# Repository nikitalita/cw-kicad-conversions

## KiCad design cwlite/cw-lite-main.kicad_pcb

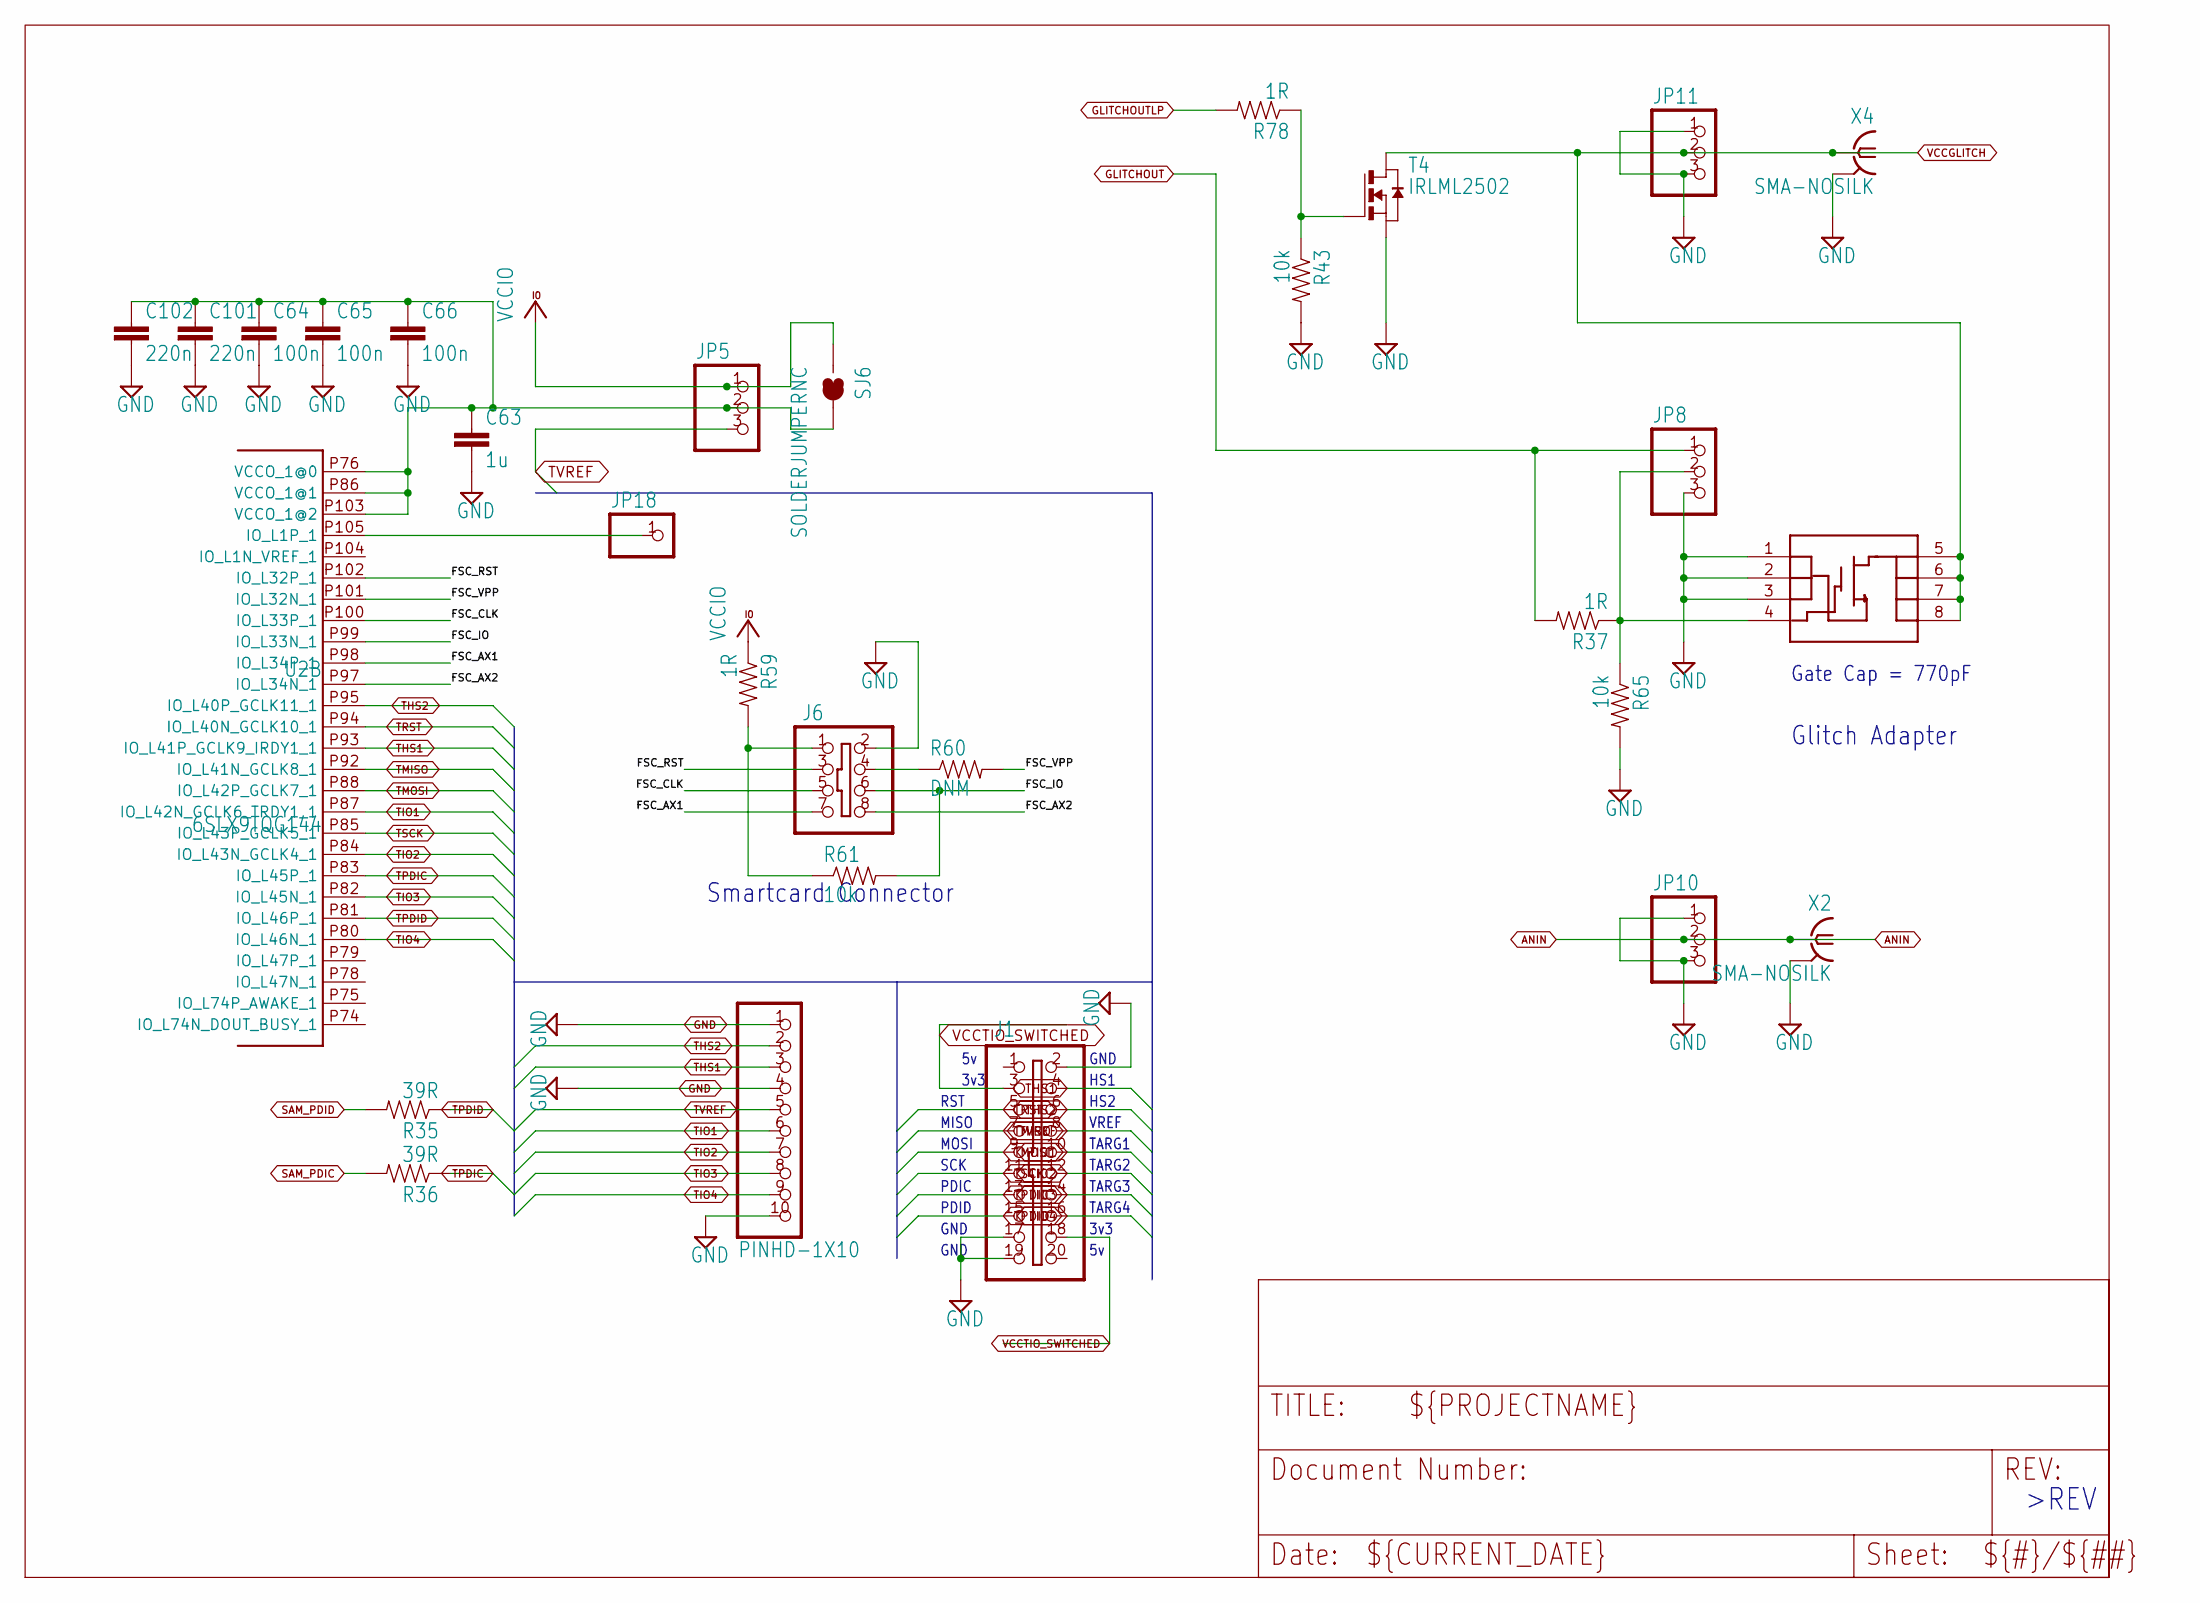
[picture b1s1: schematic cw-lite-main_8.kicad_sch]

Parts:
C63: 1u; 0603C
C64, C65, C66: 100n; 0402C
C101, C102: 220n; 0402C
J1: SHROUD_2X10-SHROUDED; PINSHRD_PTH_2X10
J6: SHROUD_2X4SHROUD; PINSHRD_PTH_2X04
JP5, JP8, JP10, JP11: PINHD-1X3; 1X03
JP9: PINHD-1X10; 1X10-BIG
JP18: PINHD-1X1; 1X01
R35, R36: 39R; 0603R
R37, R59, R78: 1R; 0603R
R43, R61, R65: 10k; 0603R
R60: DNM; 0603R
SJ6: SOLDERJUMPERNC; SJ_2S
T4: IRLML2502; SOT-23; MPN IRLML2502TRPBF
U2: 6SLX9TQG144; TQ144; MPN XC6SLX9-3TQG144C
U8: MOSFET-NCHANNEL-SOIC8; SO08
X2, X4: SMA-NOSILK; J502-ND-142-0711-821_826-NOSILK

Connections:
/cw-lite-main_8/FSC_AX1: J6.7, U2.P98 (IO_L34P_1)
/cw-lite-main_8/FSC_AX2: J6.8, U2.P97 (IO_L34N_1)
/cw-lite-main_8/FSC_CLK: J6.5, U2.P100 (IO_L33P_1)
/cw-lite-main_8/FSC_IO: J6.6, R61.2, U2.P99 (IO_L33N_1)
/cw-lite-main_8/FSC_RST: J6.3, U2.P102 (IO_L32P_1)
/cw-lite-main_8/FSC_VPP: R60.2, U2.P101 (IO_L32N_1)
ANIN: JP10.2, X2.1; also elsewhere on the board
GLITCHOUT: JP8.1, R37.2; also elsewhere on the board
GLITCHOUTLP: R78.2; also elsewhere on the board
GND: C63.2, C64.2, C65.2, C66.2, C101.2, C102.2, J1.2, J1.17, J1.19, J6.2, JP8.3, JP9.1, JP9.4, JP9.10, JP10.1, JP10.3, JP11.1, JP11.3, R43.2, R65.2, T4.2 (S), U8.1 (S@1), U8.2 (S@2), U8.3 (S@3), X2.G@1 (2), X2.G@2 (2), X2.G@3 (2), X2.G@4 (2), X4.G@1 (2), X4.G@2 (2), X4.G@3 (2), X4.G@4 (2); also elsewhere on the board
unnamed: J6.1, R59.2, R61.1
unnamed: J6.4, R60.1
unnamed: R43.1, R78.1, T4.3 (G)
unnamed: JP18.1, U2.P105 (IO_L1P_1)
unnamed: C63.1, C64.1, C65.1, C66.1, C101.1, C102.1, JP5.2, SJ6.2, U2.P76 (VCCO_1@0), U2.P86 (VCCO_1@1), U2.P103 (VCCO_1@2)
unnamed: JP8.2, R37.1, R65.1, U8.4 (G)
SAM_PDIC: R36.2; also elsewhere on the board
SAM_PDID: R35.2; also elsewhere on the board
THS1: J1.4, JP9.3, U2.P93 (IO_L41P_GCLK9_IRDY1_1); also elsewhere on the board
THS2: J1.6, JP9.2, U2.P95 (IO_L40P_GCLK11_1); also elsewhere on the board
TIO1: J1.10, JP9.6, U2.P87 (IO_L42N_GCLK6_TRDY1_1); also elsewhere on the board
TIO2: J1.12, JP9.7, U2.P84 (IO_L43N_GCLK4_1); also elsewhere on the board
TIO3: J1.14, JP9.8, U2.P82 (IO_L45N_1); also elsewhere on the board
TIO4: J1.16, JP9.9, U2.P80 (IO_L46N_1); also elsewhere on the board
TMISO: J1.7, U2.P92 (IO_L41N_GCLK8_1); also elsewhere on the board
TMOSI: J1.9, U2.P88 (IO_L42P_GCLK7_1); also elsewhere on the board
TPDIC: J1.13, R36.1, U2.P83 (IO_L45P_1); also elsewhere on the board
TPDID: J1.15, R35.1, U2.P81 (IO_L46P_1); also elsewhere on the board
TRST: J1.5, U2.P94 (IO_L40N_GCLK10_1); also elsewhere on the board
TSCK: J1.11, U2.P85 (IO_L43P_GCLK5_1); also elsewhere on the board
TVREF: J1.8, JP5.3, JP9.5; also elsewhere on the board
VCCGLITCH: JP11.2, T4.1 (D), U8.5 (D@4), U8.6 (D@3), U8.7 (D@2), U8.8 (D@1), X4.1; also elsewhere on the board
VCCIO: JP5.1, R59.1, SJ6.1; also elsewhere on the board
VCCTIO_SWITCHED: J1.3, J1.18; also elsewhere on the board

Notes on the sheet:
3v3
Glitch Adapter
VREF
PDID
RST
>REV
SCK
HS1
Smartcard Connector
TARG1
MOSI
Gate Cap = 770pF
GND
TARG2
TARG3
MISO
HS2
PDIC
TARG4

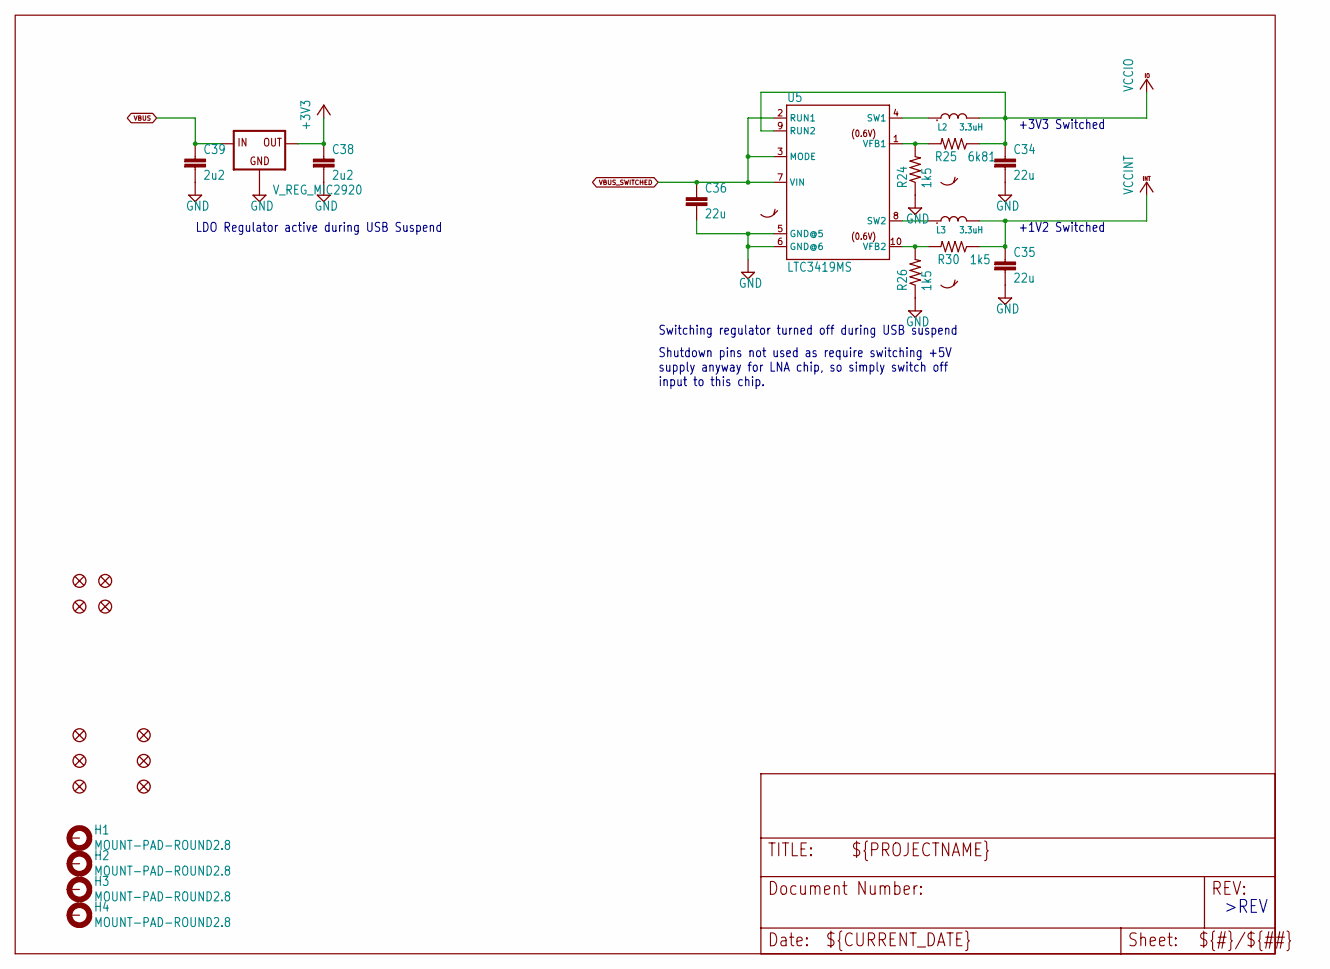
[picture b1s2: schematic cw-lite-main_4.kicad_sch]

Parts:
C34, C35, C36: 22u; 0805
C38, C39: 2u2; 0603C
FID1, FID2, FID3, FID4, FID5, FID6: FIDUCIAL1.5X3; FIDUCIAL-1.5X3
H1, H2, H3, H4: MOUNT-PAD-ROUND2.8; 2,8-PAD
L2: 3.3uH; VLS3015
L3: 3.3uH; VLS3015; MPN VLS3015ET-3R3M
MFID1, MFID2, MFID3, MFID4: FIDUCIALUFIDUCIAL; MICRO-FIDUCIAL
R24, R26, R30: 1k5; 0402R
R25: 6k81; 0402R
U5: LTC3419MS; MSOP10; MPN LTC3419EMS#PBF
U7: V_REG_MIC2920; SOT223; MPN TC1262-3.3VDBTR

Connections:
+3V3: C38.1, U7.3 (OUT); also elsewhere on the board
GND: C34.2, C35.2, C36.2, C38.2, C39.2, R24.1, R26.1, U5.5 (GND@5), U5.6 (GND@6), U7.2 (GND); also elsewhere on the board
unnamed: L2.1, U5.4 (SW1)
unnamed: L3.1, U5.8 (SW2)
unnamed: R24.2, R25.2, U5.1 (VFB1)
unnamed: R26.2, R30.2, U5.10 (VFB2)
VBUS: C39.1, U7.1 (IN); also elsewhere on the board
VBUS_SWITCHED: C36.1, U5.2 (RUN1), U5.3 (MODE), U5.7 (VIN); also elsewhere on the board
VCCINT: C35.1, L3.2, R30.1; also elsewhere on the board
VCCIO: C34.1, L2.2, R25.1, U5.9 (RUN2); also elsewhere on the board

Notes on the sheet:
Switching regulator turned off during USB suspend
LDO Regulator active during USB Suspend
+3V3 Switched
>REV
+1V2 Switched
Shutdown pins not used as require switching +5V supply anyway for LNA chip, so simply switch off input to this chip.

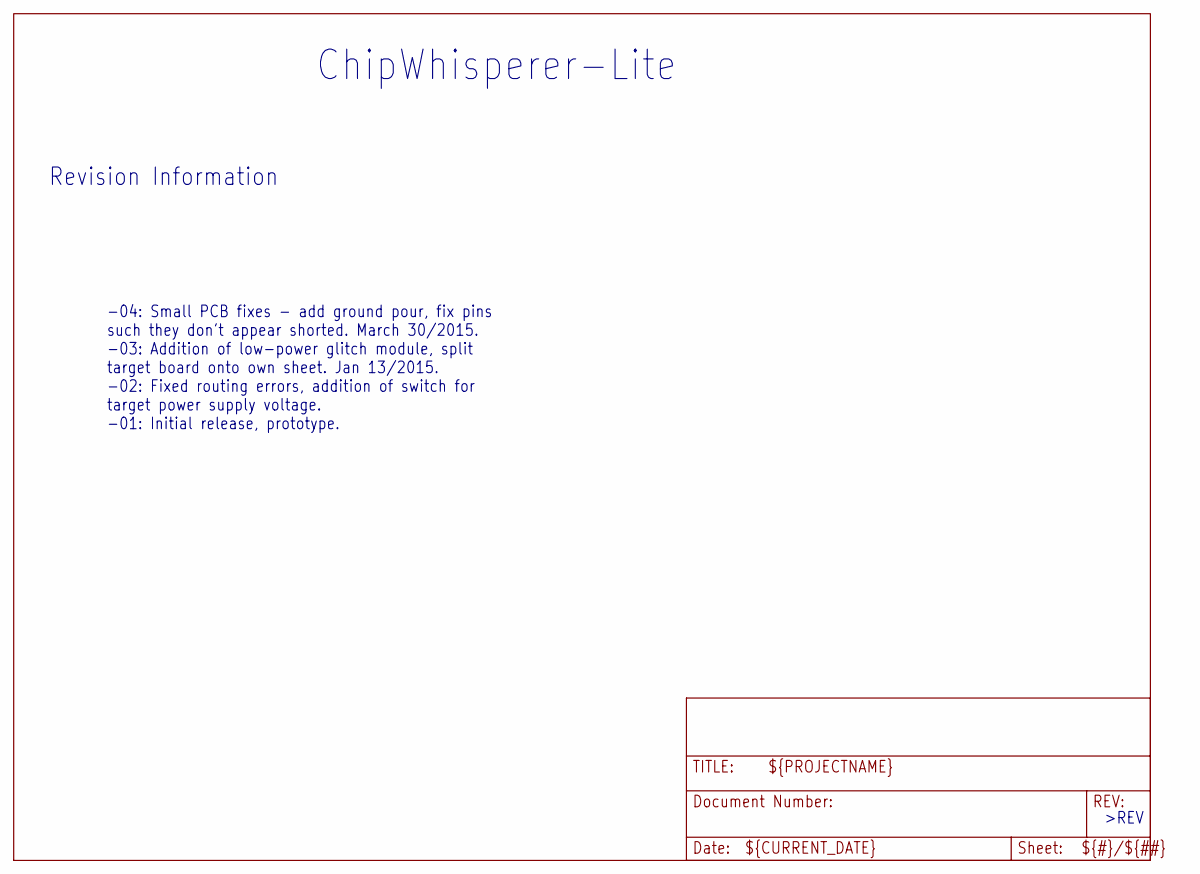
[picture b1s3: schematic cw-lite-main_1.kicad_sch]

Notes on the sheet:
ChipWhisperer-Lite
-04: Small PCB fixes - add ground pour, fix pins such they don't appear shorted. March 30/2015. -03: Addition of low-power glitch module, split target board onto own sheet. Jan 13/2015. -02: Fixed routing errors, addition of switch for target power supply voltage. -01: Initial release, prototype.
>REV
Revision Information

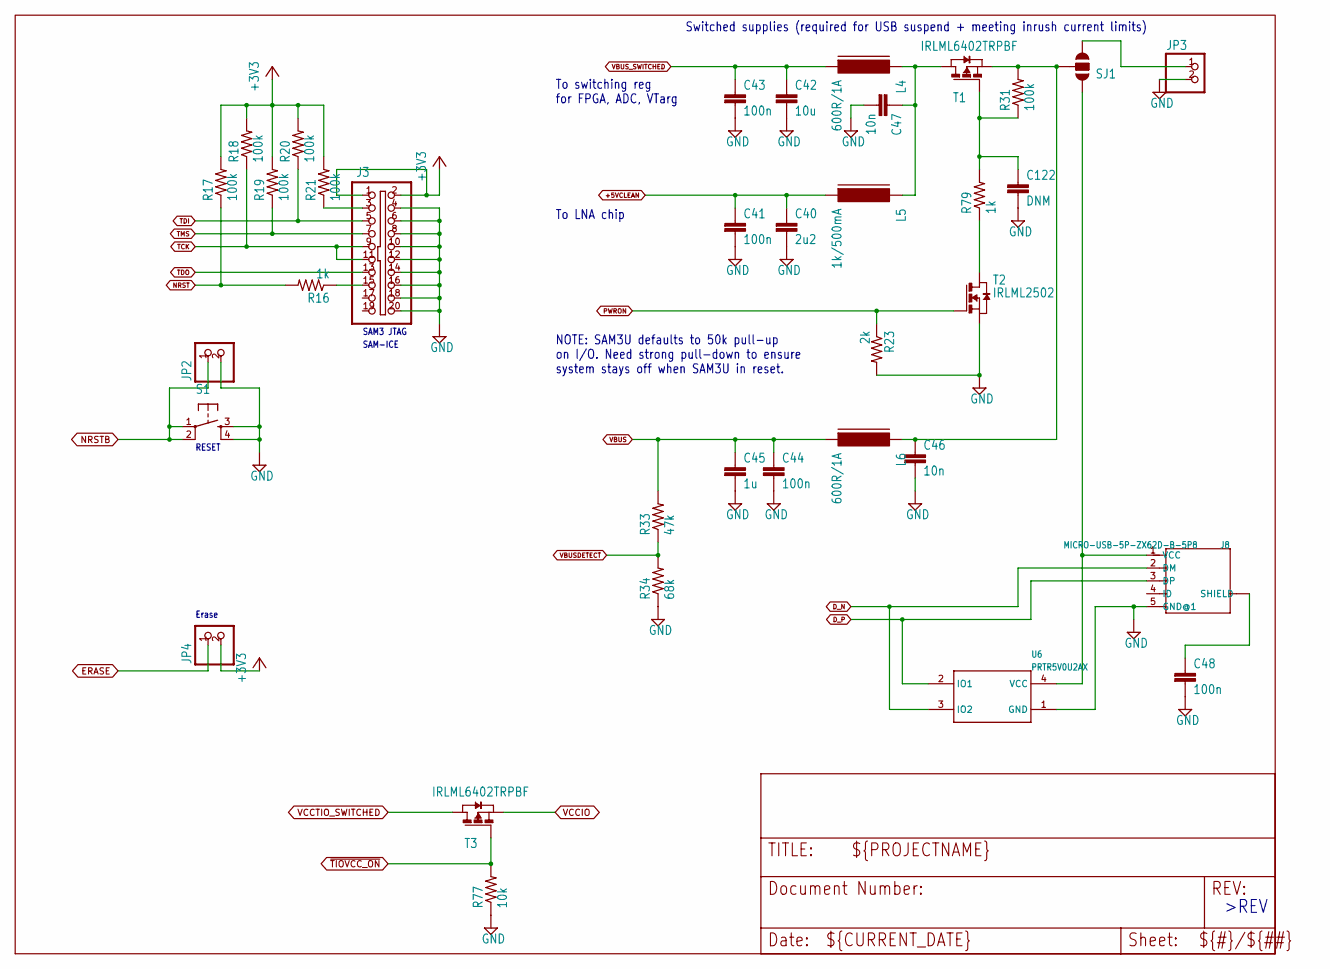
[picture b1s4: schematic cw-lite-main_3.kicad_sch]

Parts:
C40: 2u2; 0603C
C41, C43, C44, C48: 100n; 0603C
C42: 10u; 0603C
C45: 1u; 0603C
C46, C47: 10n; 0603C
C122: DNM; 0603C
J3: SHROUD_2X10-SHROUDED; PINSHRD_PTH_2X10
J8: MICRO-USB-5P-ZX62D-B-5P8; B-SMD-5P-TH; MPN ZX62D-B-5P8
JP2, JP3, JP4: PINHD-1X2; 1X02
L4, L6: 600R/1A; FB603
L5: 1k/500mA; FB603
R16: 1k; 0402R
R17, R18, R19, R20, R21, R31: 100k; 0402R
R23: 2k; 0603R
R33: 47k; 0402R
R34: 68k; 0402R
R77: 10k; 0402R
R79: 1k; 0603R
S1: TAC_SWITCHSMD; TACTILE_SWITCH_SMD
SJ1: SOLDERJUMPER_2WAYPASTE1&2; SJ_3_PASTE1&2
T1, T3: IRLML6402TRPBF; SOT-23; MPN IRLML6402TRPBF
T2: IRLML2502; SOT-23; MPN IRLML2502TRPBF
U6: PRTR5V0U2AX; SOT143B; MPN PRTR5V0U2AX,215

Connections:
+3V3: J3.1, J3.2, JP4.2, R17.2, R18.2, R19.2, R20.2, R21.2; also elsewhere on the board
+5VCLEAN: C40.1, C41.1, L5.2; also elsewhere on the board
D_N: J8.2 (DM), U6.3 (IO2); also elsewhere on the board
D_P: J8.3 (DP), U6.2 (IO1); also elsewhere on the board
ERASE: JP4.1; also elsewhere on the board
GND: C40.2, C41.2, C42.2, C43.2, C44.2, C45.2, C46.2, C47.2, C48.2, C122.2, J3.4, J3.6, J3.8, J3.10, J3.12, J3.14, J3.16, J3.18, J3.20, J8.5 (GND@1), JP2.2, JP3.2, R23.2, R34.1, R77.1, S1.3, S1.4, T2.2 (S), U6.1 (GND); also elsewhere on the board
NRST: R16.2, R17.1; also elsewhere on the board
NRSTB: JP2.1, S1.1, S1.2; also elsewhere on the board
unnamed: C48.1, J8.E1 (SHIELD), J8.E2 (SHIELD), J8.P$1 (SHIELD), J8.P$2 (SHIELD), J8.P$3 (SHIELD), J8.P$4 (SHIELD)
unnamed: J3.3, R21.1
unnamed: J3.15, R16.1
unnamed: J8.1 (VCC), SJ1.1, U6.4 (VCC)
unnamed: JP3.1, SJ1.3
unnamed: C47.1, L4.1, L5.1, T1.1 (D)
unnamed: C122.1, R31.1, R79.2, T1.3 (G)
unnamed: C46.1, L6.1, R31.2, SJ1.2, T1.2 (S)
unnamed: R79.1, T2.1 (D)
PWRON: R23.1, T2.3 (G); also elsewhere on the board
TCK: J3.9, J3.11, R18.1; also elsewhere on the board
TDI: J3.5, R20.1; also elsewhere on the board
TDO: J3.13; also elsewhere on the board
TMS: J3.7, R19.1; also elsewhere on the board
VBUS: C44.1, C45.1, L6.2, R33.2; also elsewhere on the board
VBUSDETECT: R33.1, R34.2; also elsewhere on the board
VBUS_SWITCHED: C42.1, C43.1, L4.2; also elsewhere on the board
VCCIO: T3.2 (S); also elsewhere on the board
VCCTIO_SWITCHED: T3.1 (D); also elsewhere on the board
~TIOVCC_ON: R77.2, T3.3 (G); also elsewhere on the board

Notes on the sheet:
To switching reg for FPGA, ADC, VTarg
NOTE: SAM3U defaults to 50k pull-up on I/O. Need strong pull-down to ensure system stays off when SAM3U in reset.
To LNA chip
SAM3 JTAG
Erase
SAM-ICE
Switched supplies (required for USB suspend + meeting inrush current limits)
RESET
>REV

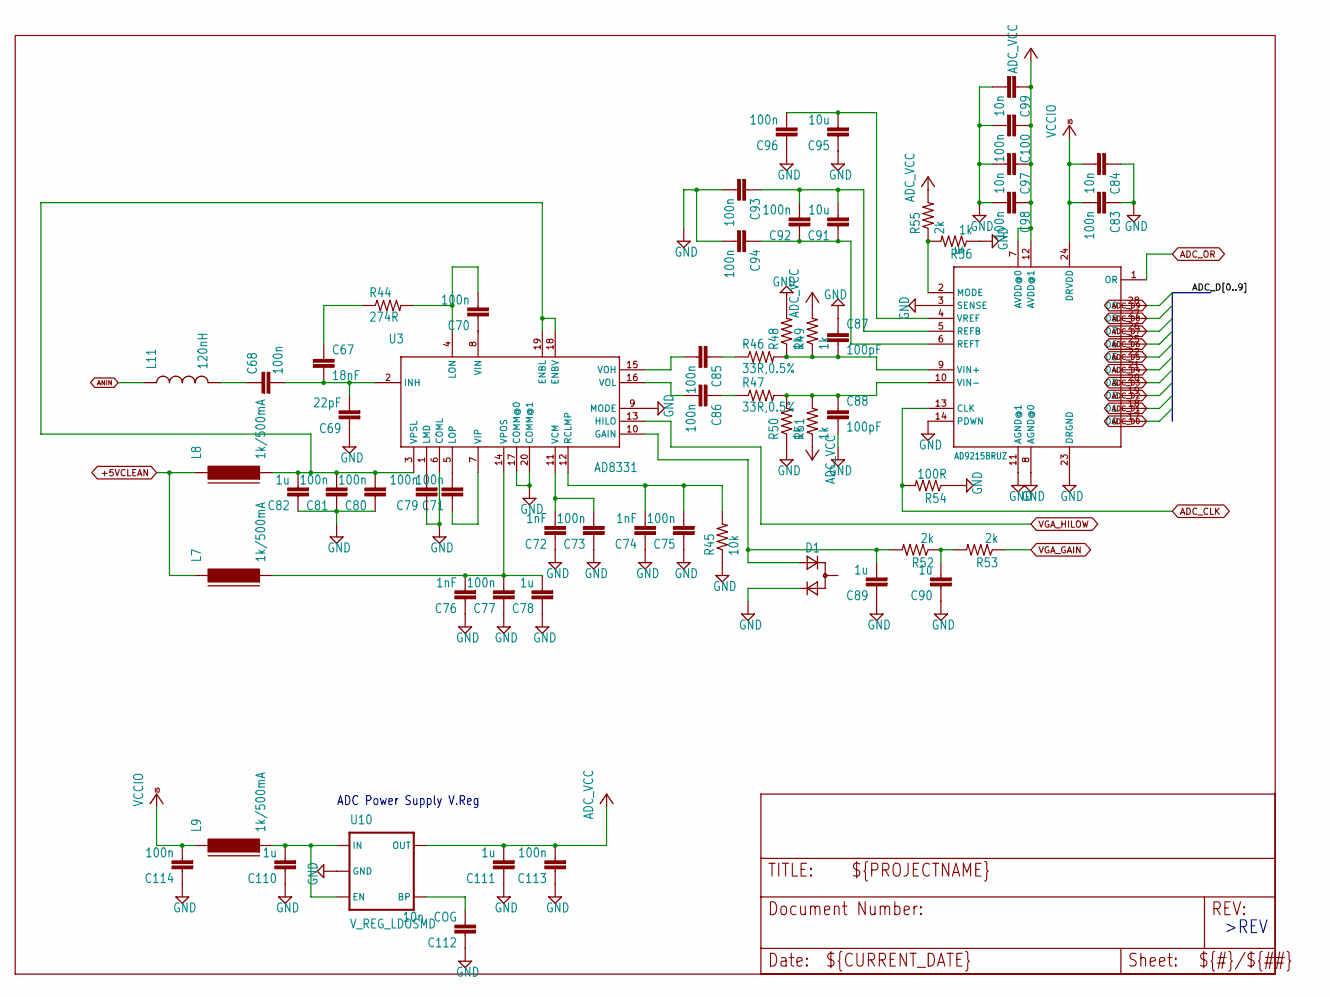
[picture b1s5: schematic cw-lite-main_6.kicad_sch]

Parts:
C67: 18nF; 0603C
C68, C85, C86: 100n; 0603C
C69: 22pF; 0603C
C70, C71, C73, C75, C77, C79, C80, C81, C83, C92, C93, C94, C96, C98, C100, C113, C114: 100n; 0402C
C72, C74, C76: 1nF; 0402C
C78, C82, C89, C90, C110, C111: 1u; 0603C
C84, C97, C99: 10n; 0402C
C87, C88: 100pF; 0603C
C91, C95: 10u; 0603C
C112: 10n, COG; 0402C
D1: D_ACACSOT23; SOT-23; MPN BAV99-7F
L7, L8, L9: 1k/500mA; FB603
L11: 120nH; 0603
R44: 274R; 0603R
R45: 10k; 0603R
R46, R47: 33R,0.5%; 0603R
R48, R49, R50, R51: 1k; 0402R
R52, R53, R55: 2k; 0603R
R54: 100R; 0603R
R56: 1k; 0603R
U3: AD8331; QSOP20; MPN AD8331ARQZ
U4: AD9215BRUZ; TSSOP28; MPN AD9215BRUZ-105
U10: V_REG_LDOSMD; SOT23-5; MPN LP3985IM5X-3.0/NOPB

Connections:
+5VCLEAN: L7.1, L8.1; also elsewhere on the board
ADC_CLK: R54.2, U4.13 (CLK); also elsewhere on the board
ADC_D0: U4.17 (D0); also elsewhere on the board
ADC_D1: U4.18 (D1); also elsewhere on the board
ADC_D2: U4.19 (D2); also elsewhere on the board
ADC_D3: U4.20 (D3); also elsewhere on the board
ADC_D4: U4.21 (D4); also elsewhere on the board
ADC_D5: U4.22 (D5); also elsewhere on the board
ADC_D6: U4.25 (D6); also elsewhere on the board
ADC_D7: U4.26 (D7); also elsewhere on the board
ADC_D8: U4.27 (D8); also elsewhere on the board
ADC_D9: U4.28 (D9); also elsewhere on the board
ADC_OR: U4.1 (OR); also elsewhere on the board
ADC_VCC: C97.1, C98.1, C99.1, C100.1, C111.2, C113.2, R49.2, R51.1, R55.2, U4.7 (AVDD@0), U4.12 (AVDD@1), U10.5 (OUT)
ANIN: L11.1; also elsewhere on the board
GND: C69.1, C72.1, C73.1, C74.1, C75.1, C76.1, C77.1, C78.1, C79.1, C80.1, C81.1, C82.1, C83.1, C84.1, C87.1, C88.2, C89.1, C90.1, C93.2, C94.2, C95.1, C96.1, C97.2, C98.2, C99.2, C100.2, C110.1, C111.1, C112.1, C113.1, C114.1, D1.2 (C), R45.1, R48.2, R50.1, R54.1, R56.1, U3.6 (COML), U3.9 (MODE), U3.17 (COMM@0), U3.20 (COMM@1), U4.3 (SENSE), U4.8 (AGND@0), U4.11 (AGND@1), U4.14 (PDWN), U4.23 (DRGND), U10.2 (GND); also elsewhere on the board
unnamed: C67.1, R44.1
unnamed: C68.1, L11.2
unnamed: C85.1, R46.1
unnamed: C86.1, R47.1
unnamed: C90.2, R52.1, R53.2
unnamed: C89.2, D1.3 (A), R52.2, U3.10 (GAIN)
unnamed: C80.2, C81.2, C82.2, L8.2, U3.3 (VPSL), U3.18 (ENBV), U3.19 (ENBL)
unnamed: C67.2, C68.2, C69.2, U3.2 (INH)
unnamed: C79.2, U3.1 (LMD)
unnamed: C70.2, R44.2, U3.4 (LON)
unnamed: C71.2, U3.5 (LOP)
unnamed: C74.2, C75.2, R45.2, U3.12 (RCLMP)
unnamed: C72.2, C73.2, U3.11 (VCM)
unnamed: C70.1, U3.8 (VIN)
unnamed: C71.1, U3.7 (VIP)
unnamed: C85.2, U3.15 (VOH)
unnamed: C86.2, U3.16 (VOL)
unnamed: C76.2, C77.2, C78.2, L7.2, U3.14 (VPOS)
unnamed: R55.1, R56.2, U4.2 (MODE)
unnamed: C91.2, C92.2, C93.1, U4.5 (REFB)
unnamed: C91.1, C92.1, C94.1, U4.6 (REFT)
unnamed: C87.2, R46.2, R48.1, R49.1, U4.9 (VIN+)
unnamed: C88.1, R47.2, R50.2, R51.2, U4.10 (VIN-)
unnamed: C95.2, C96.2, U4.4 (VREF)
unnamed: C112.2, U10.4 (BP)
unnamed: C110.2, L9.2, U10.1 (IN), U10.3 (EN)
VCCIO: C83.2, C84.2, C114.2, L9.1, U4.24 (DRVDD); also elsewhere on the board
VGA_GAIN: R53.1; also elsewhere on the board
VGA_HILOW: U3.13 (HILO); also elsewhere on the board

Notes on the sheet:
>REV
ADC Power Supply V.Reg

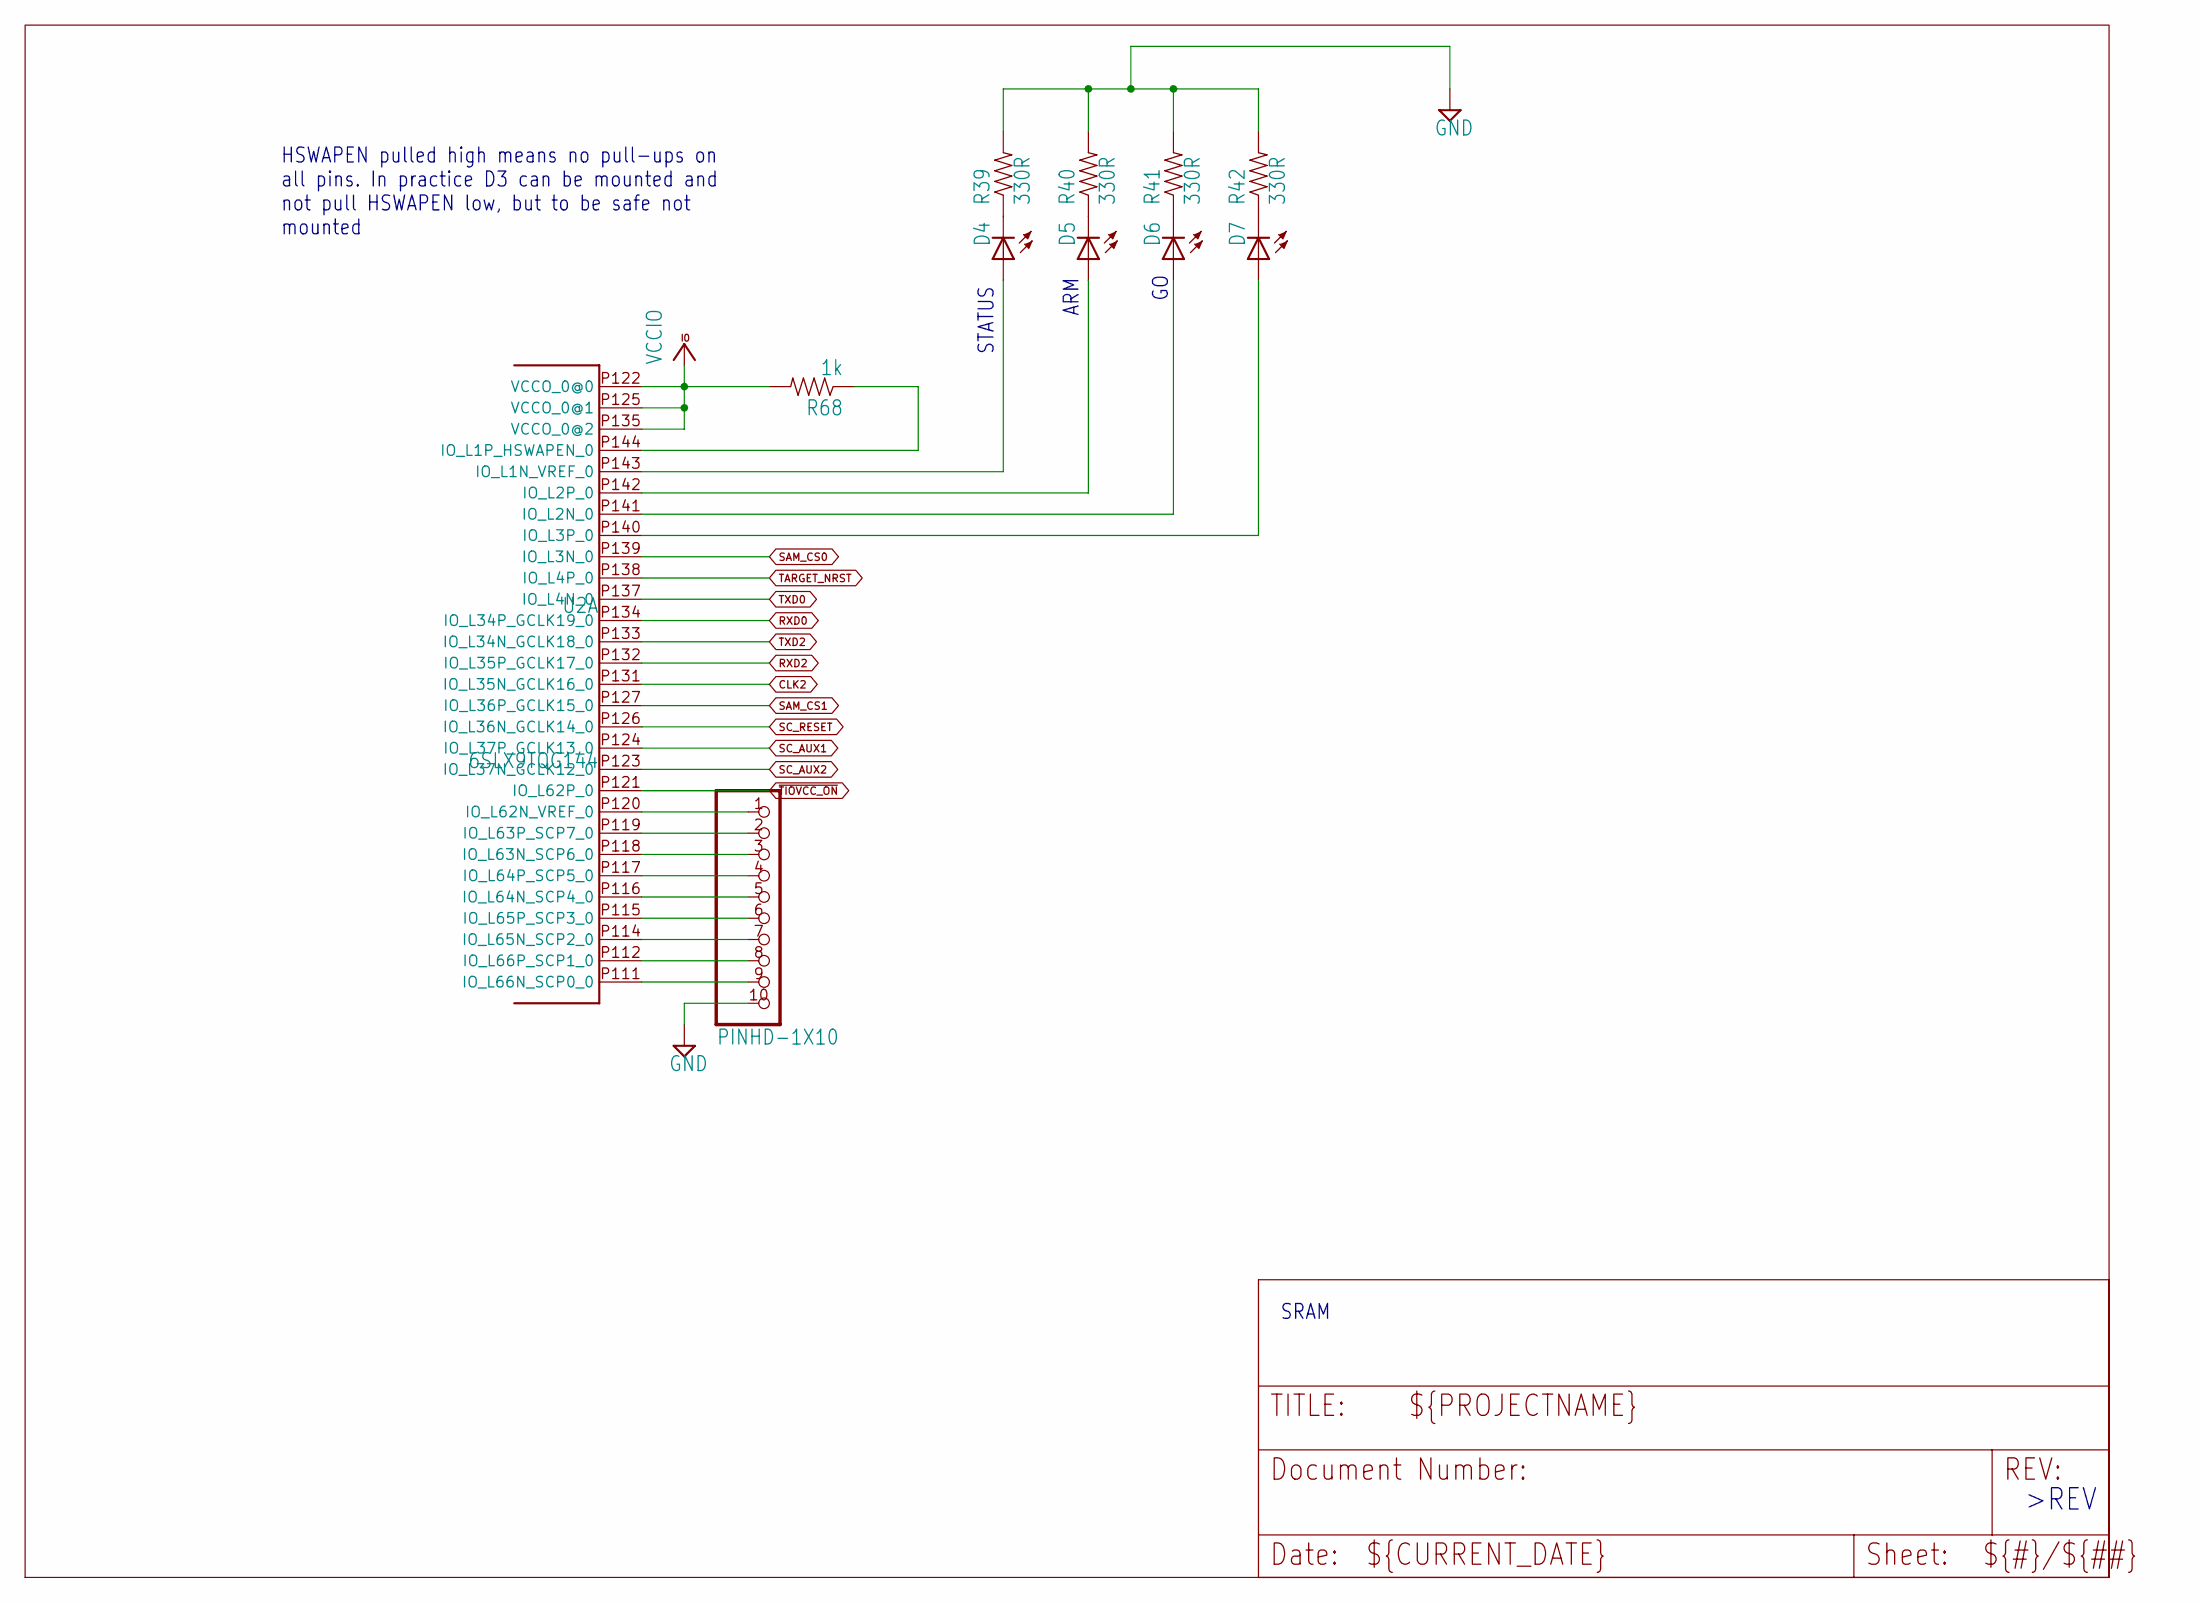
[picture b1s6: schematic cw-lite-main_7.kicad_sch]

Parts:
D4, D5, D6, D7: LED0603; LED-0603
J5: PINHD-1X10; 1X10-BIG
R39, R40, R41, R42: 330R; 0402R
R68: 1k; 0402R
U2: 6SLX9TQG144; TQ144; MPN XC6SLX9-3TQG144C

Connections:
CLK2: U2.P131 (IO_L35N_GCLK16_0); also elsewhere on the board
GND: J5.10, R39.2, R40.2, R41.2, R42.2; also elsewhere on the board
unnamed: D4.C, R39.1
unnamed: D5.C, R40.1
unnamed: D6.C, R41.1
unnamed: D7.C, R42.1
unnamed: D4.A, U2.P143 (IO_L1N_VREF_0)
unnamed: R68.1, U2.P144 (IO_L1P_HSWAPEN_0)
unnamed: D6.A, U2.P141 (IO_L2N_0)
unnamed: D5.A, U2.P142 (IO_L2P_0)
unnamed: D7.A, U2.P140 (IO_L3P_0)
unnamed: J5.1, U2.P120 (IO_L62N_VREF_0)
unnamed: J5.3, U2.P118 (IO_L63N_SCP6_0)
unnamed: J5.2, U2.P119 (IO_L63P_SCP7_0)
unnamed: J5.5, U2.P116 (IO_L64N_SCP4_0)
unnamed: J5.4, U2.P117 (IO_L64P_SCP5_0)
unnamed: J5.7, U2.P114 (IO_L65N_SCP2_0)
unnamed: J5.6, U2.P115 (IO_L65P_SCP3_0)
unnamed: J5.9, U2.P111 (IO_L66N_SCP0_0)
unnamed: J5.8, U2.P112 (IO_L66P_SCP1_0)
RXD0: U2.P134 (IO_L34P_GCLK19_0); also elsewhere on the board
RXD2: U2.P132 (IO_L35P_GCLK17_0); also elsewhere on the board
SAM_CS0: U2.P139 (IO_L3N_0); also elsewhere on the board
SAM_CS1: U2.P127 (IO_L36P_GCLK15_0); also elsewhere on the board
SC_AUX1: U2.P124 (IO_L37P_GCLK13_0); also elsewhere on the board
SC_AUX2: U2.P123 (IO_L37N_GCLK12_0); also elsewhere on the board
SC_RESET: U2.P126 (IO_L36N_GCLK14_0); also elsewhere on the board
TARGET_NRST: U2.P138 (IO_L4P_0); also elsewhere on the board
TXD0: U2.P137 (IO_L4N_0); also elsewhere on the board
TXD2: U2.P133 (IO_L34N_GCLK18_0); also elsewhere on the board
VCCIO: R68.2, U2.P122 (VCCO_0@0), U2.P125 (VCCO_0@1), U2.P135 (VCCO_0@2); also elsewhere on the board
~TIOVCC_ON: U2.P121 (IO_L62P_0); also elsewhere on the board

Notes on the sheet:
>REV
ARM
SRAM
STATUS
HSWAPEN pulled high means no pull-ups on all pins. In practice D3 can be mounted and not pull HSWAPEN low, but to be safe not mounted

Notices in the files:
cwlite/cw-lite-main.kicad_pcb:
Copyright NewAE Technology Inc.
